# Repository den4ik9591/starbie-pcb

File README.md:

[README-BOM-section.md](https://github.com/user-attachments/files/33780172/README-BOM-section.md)
# My Starbie

A tiny star-shaped desk pet. A XIAO ESP32-C3 draws a wandering pet on a 0.96" OLED screen. You can open a radial menu with a button, tilt the board to pick an action, and check the room temperature and humidity on a stats screen.

I made this for Half Life Week 1, following the Starbie guide, and then changed it to make it my own.

## What I changed

- **Star-shaped board:** I drew my own star outline on the Edge.Cuts layer in KiCad, so the PCB itself is a star.
- **New menu action:** I replaced PET with **DANCE**, a more energetic move with its own joy/energy/fullness values.
- **Sparkle trail:** I added a `drawSparkle` function so a little star blinks behind the pet as it walks. It fits the star-shaped board.
- **Pull-up resistor:** the guide's written steps left out the 10k resistor on the DHT11 data line, so I found it in the guide's screenshot and wired it to 3.3V.

## Images

## Hardware

- Microcontroller: Seeed Studio XIAO ESP32-C3
- Display: 0.96" 128x64 I2C OLED (4-pin header)
- Motion sensor: MPU6050 module (8-pin header, shares the I2C lines with the OLED)
- Environment sensor: DHT11, with a 10k pull-up resistor on the data line
- Controls: 2 push buttons (Cherry MX style footprints)
- Board: custom star-shaped PCB designed in KiCad

### Pin connections

| Part | XIAO pin | ESP32-C3 GPIO |
| --- | --- | --- |
| OLED SDA and MPU6050 SDA | D4 | GPIO6 |
| OLED SCL and MPU6050 SCL | D5 | GPIO7 |
| DHT11 data | D1 | GPIO3 |
| Button 1 | D2 | GPIO4 |
| Button 2 | D3 | GPIO5 |

## Controls

| Control | What it does |
| --- | --- |
| Button 1, first press | Opens the radial menu |
| Tilt while the menu is open | Moves the selector ball |
| Button 1, second press | Chooses the highlighted action (NAP, PLAY, FEED, DANCE) |
| Button 2 | Shows or hides the stats screen |
| Shake the board | Gives the pet a shake reaction |

## Files

-  `HalfLife10weeks/Hardware/Starbie/`: KiCad project (schematic and PCB)
- `HalfLife10weeks/Hardware/`: imported footprints (`Imported Parts.pretty`), symbol library and 3D models
- `HalfLife10weeks/Gerbers/`: manufacturing files for the PCB
- `HalfLife10weeks/Firmware/StarbieCode/`: Arduino sketch
- `HalfLife10weeks/Images/`: screenshots of the design

## Firmware

The code is an Arduino sketch based on the starter code from the Half Life Week 1 guide.

To upload it:
1. Install the Arduino IDE.
2. Add the ESP32 board package URL in File > Preferences: `https://espressif.github.io/arduino-esp32/package_esp32_index.json`
3. In Boards Manager, install **esp32 by Espressif Systems**, then select the board **XIAO_ESP32C3**.
4. Install the libraries: Adafruit GFX Library, Adafruit SSD1306, Adafruit MPU6050 and DHT sensor library.
5. Open `HalfLife10weeks/Firmware/StarbieCode/StarbieCode.ino` and upload.

6. To open the project in KiCad, first add Hardware/Imported Parts.pretty (footprints) and Hardware/Seeed_Studio_XIAO_Series.kicad_sym (symbols) under Preferences → Manage Footprint/Symbol Libraries.

## Status

- [x] Schematic finished
- [x] PCB routed and DRC checked
- [X] Gerbers exported
- [ ] Parts ordered and board built
- [ ] Firmware tested on real hardware

## What I learned

- How to use KiCad: drawing a schematic, assigning footprints, routing a board and running DRC.
- How to add imported footprint and symbol libraries.
- Why a DHT11 needs a pull-up resistor, and how to read a netlist log to find wiring mistakes.
- How to draw a custom board outline.

## What I'd improve

- Add a battery and a switch so it works without USB.
- Design a 3D-printed case in Fusion 360 for it.
- Draw my own pet sprite instead of the starter one.

- [Uploading README-BOM-section.md…]()
## Bill of Materials

Full file: [`bom.csv`](bom.csv). Prices converted from GBP to USD at 1 GBP = 1.3386 USD (21 Oct 2026).

| Name | Purpose | Qty | Unit cost (USD) | Total (USD) | Vendor |
| --- | --- | --- | --- | --- | --- |
| ESP32 C3 SuperMini | Main microcontroller | 1 | $2.66 | $2.66 | AliExpress |
| 0.96in 128x64 I2C OLED | Pet display | 1 | $2.60 | $2.60 | UMLIFE Store (AliExpress) |
| GY-521 MPU6050 module | Tilt and shake sensing | 1 | $2.16 | $2.16 | ZAVE Official Store (AliExpress) |
| DHT11 module (KY-015) | Temperature and humidity | 1 | $1.49 | $1.49 | ZAVE Official Store (AliExpress) |
| Pin headers 2.54mm (10pcs) | Mounting OLED and MPU6050 | 1 | $1.19 | $1.19 | Sincere Company Store (AliExpress) |
| Custom star PCB (5 boards min) | Main board | 1 | $10.60 | $10.60 | JLCPCB |
| PCB shipping | Global Standard Direct Line | 1 | $6.43 | $6.43 | JLCPCB |
| **Total** | | | | **$27.13** | |

## Credits

Based on the Starbie example project and Week 1 guide from Half Life by SharKingStudios: https://github.com/SharKingStudios/Starbie

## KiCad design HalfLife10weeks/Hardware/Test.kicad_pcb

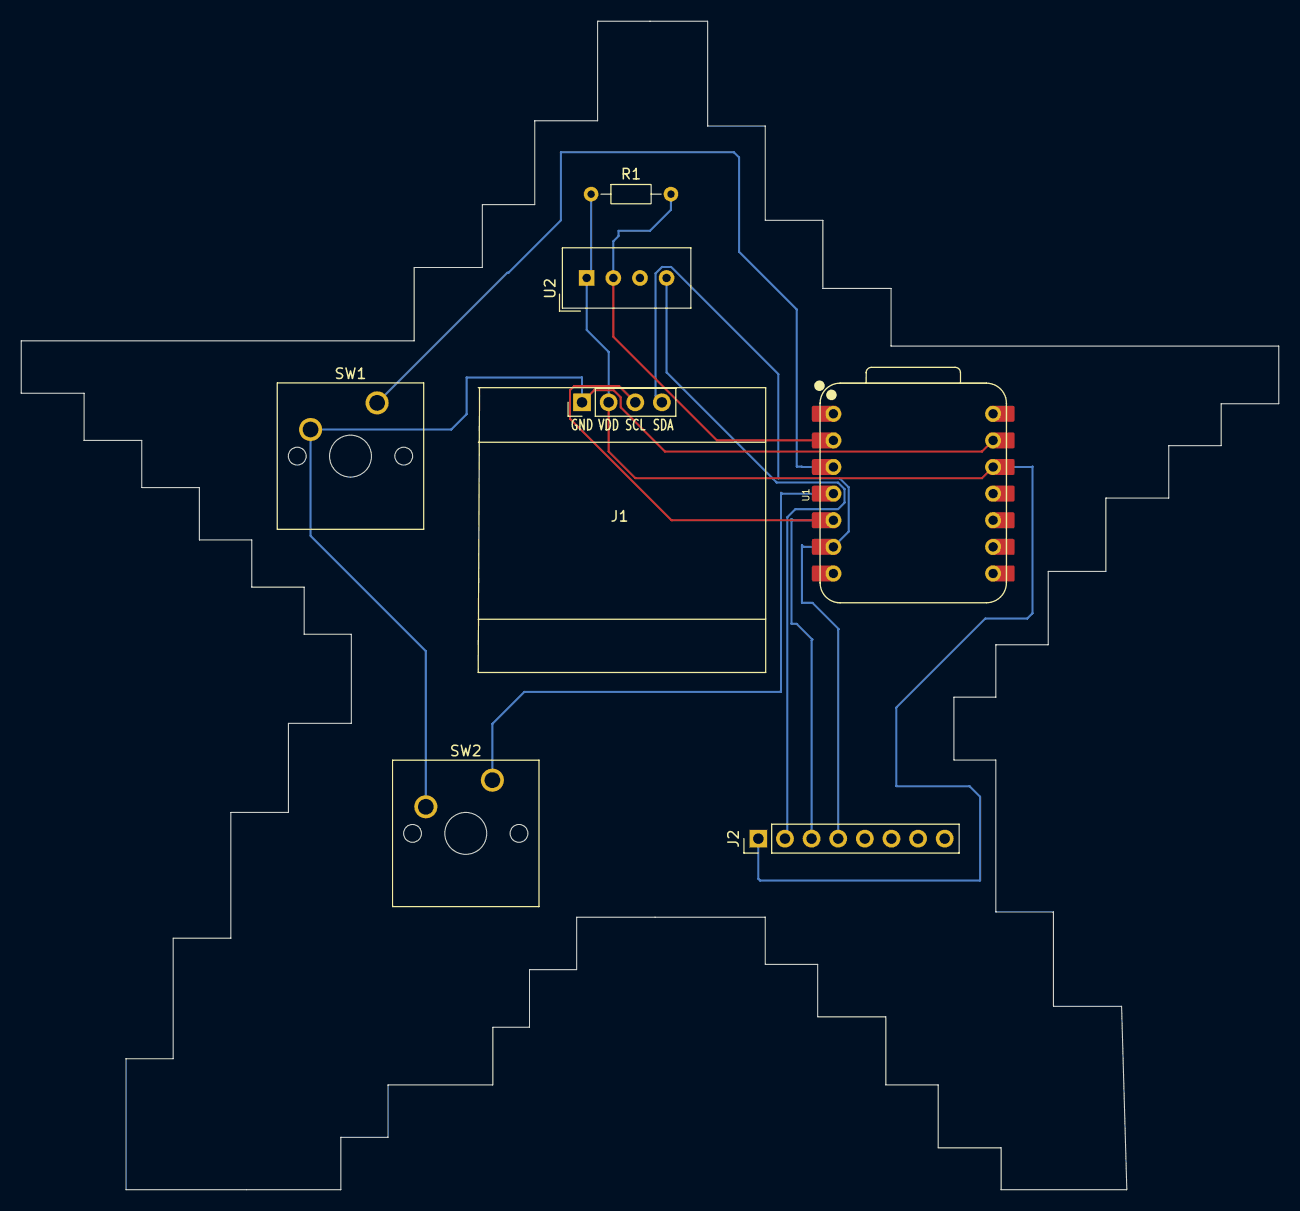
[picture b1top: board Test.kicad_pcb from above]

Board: 2 copper layers, 120.0 x 111.5 mm, 7 parts (0 on the bottom side), 8 nets.

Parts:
J1: Conn_01x04_Pin; Display_128x64_096_I2C
J2: Conn_01x08_Pin; PinHeader_1x08_P2.54mm_Vertical
R1: 10k; R_Axial_DIN0204_L3.6mm_D1.6mm_P7.62mm_Horizontal
SW1, SW2: SW_Push; SW_Cherry_MX_1.00u_PCB
U1: XIAO-ESP32-C3-SMD; XIAO-ESP32-C6-DIP
U2: DHT11; Aosong_DHT11_5.5x12.0_P2.54mm

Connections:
unnamed: J1.1, SW1.2, SW2.2, U1.13 (GND)
unnamed: J1.2, J2.1, R1.1, U1.12 (3V3_OUT), U2.1 (VDD)
unnamed: J1.3, J2.3, U1.5 (D4)
unnamed: J1.4, J2.4, U1.6 (D5)
unnamed: J2.2, U2.4 (GND)
unnamed: R1.2, U1.2 (D1), U2.2 (DATA)
unnamed: SW1.1, U1.3 (D2)
unnamed: SW2.1, U1.4 (D3)
